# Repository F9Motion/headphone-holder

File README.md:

# Headphone Holder
A RGB cylender type headphone holder for airpods max type headphones.

# Why I did this
I ddin't know what to did today and take idea from forge keeper.
# Features
* Minimalistic design
* Wireless
* With RGB diodes
* Custom
# How it works
Raspberry pi pico do all work. It put to diodes signals and control them. MCP83731 is for battery and charge the battery.
# How to assemble
1. Print PCB from **JLCPCB**
2. Print **CAD** files
3. Order microcontrollers from **BOM** and solder it to PCB
4. Flash
# How to Flash
1. Install arduino IDE
2. Download firmware
3. Connect your PC to Raspberry pi pico
4. Upload firmware
# Bill Of Materials(BOM)
|Name             |Price|Link                     |
|-----------------|-----|-------------------------|
|Printing PCB     |$2   |JLCPCB no link           |
|Raspberry pi pico|$3.48|https://ali.click/eaneq1g|
|mcp73831         |$0.58|https://ali.click/mgneq13|
|Battery          |$7.26|https://ali.click/jpneq1o|
|bottom.step      |$0.6 |felament price           |
|top.step         |$1,19|felament price           |
# Credits
All work: Rasul

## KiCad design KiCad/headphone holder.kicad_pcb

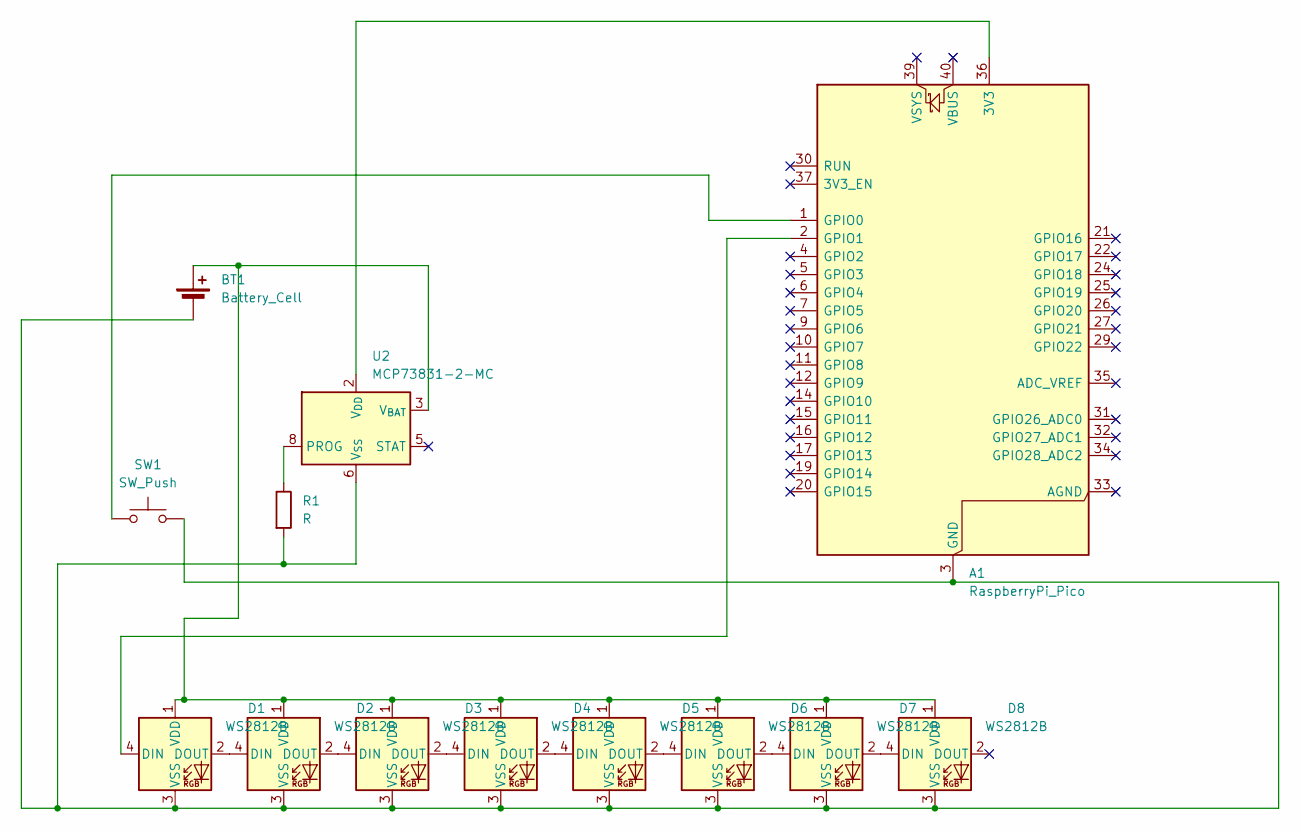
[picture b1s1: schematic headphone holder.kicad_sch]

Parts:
A1: RaspberryPi_Pico; RaspberryPi_Pico_Common_Unspecified
BT1: Battery_Cell; JST_PH_B2B-PH-K_1x02_P2.00mm_Vertical
D1, D2, D3, D4, D5, D6, D7, D8: WS2812B; LED_WS2812B_PLCC4_5.0x5.0mm_P3.2mm
R1: R; R_0201_0603Metric
SW1: SW_Push; SW_Cherry_MX_1.00u_PCB
U2: MCP73831-2-MC; DFN-8-1EP_3x2mm_P0.5mm_EP1.7x1.4mm

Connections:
unnamed: A1.36 (3V3), U2.1 (V_{DD}), U2.2 (V_{DD})
unnamed: A1.1 (GPIO0), SW1.1
unnamed: A1.2 (GPIO1), D1.4 (DIN)
unnamed: BT1.1 (+), D1.1 (VDD), D2.1 (VDD), D3.1 (VDD), D4.1 (VDD), D5.1 (VDD), D6.1 (VDD), D7.1 (VDD), D8.1 (VDD), U2.3 (V_{BAT}), U2.4 (V_{BAT})
unnamed: A1.3 (GND), A1.8 (GND), A1.13 (GND), A1.18 (GND), A1.23 (GND), A1.28 (GND), A1.38 (GND), BT1.2 (-), D1.3 (VSS), D2.3 (VSS), D3.3 (VSS), D4.3 (VSS), D5.3 (VSS), D6.3 (VSS), D7.3 (VSS), D8.3 (VSS), R1.2, SW1.2, U2.6 (V_{SS})
unnamed: D1.2 (DOUT), D2.4 (DIN)
unnamed: D2.2 (DOUT), D3.4 (DIN)
unnamed: D3.2 (DOUT), D4.4 (DIN)
unnamed: D4.2 (DOUT), D5.4 (DIN)
unnamed: D5.2 (DOUT), D6.4 (DIN)
unnamed: D6.2 (DOUT), D7.4 (DIN)
unnamed: D7.2 (DOUT), D8.4 (DIN)
unnamed: R1.1, U2.8 (PROG)

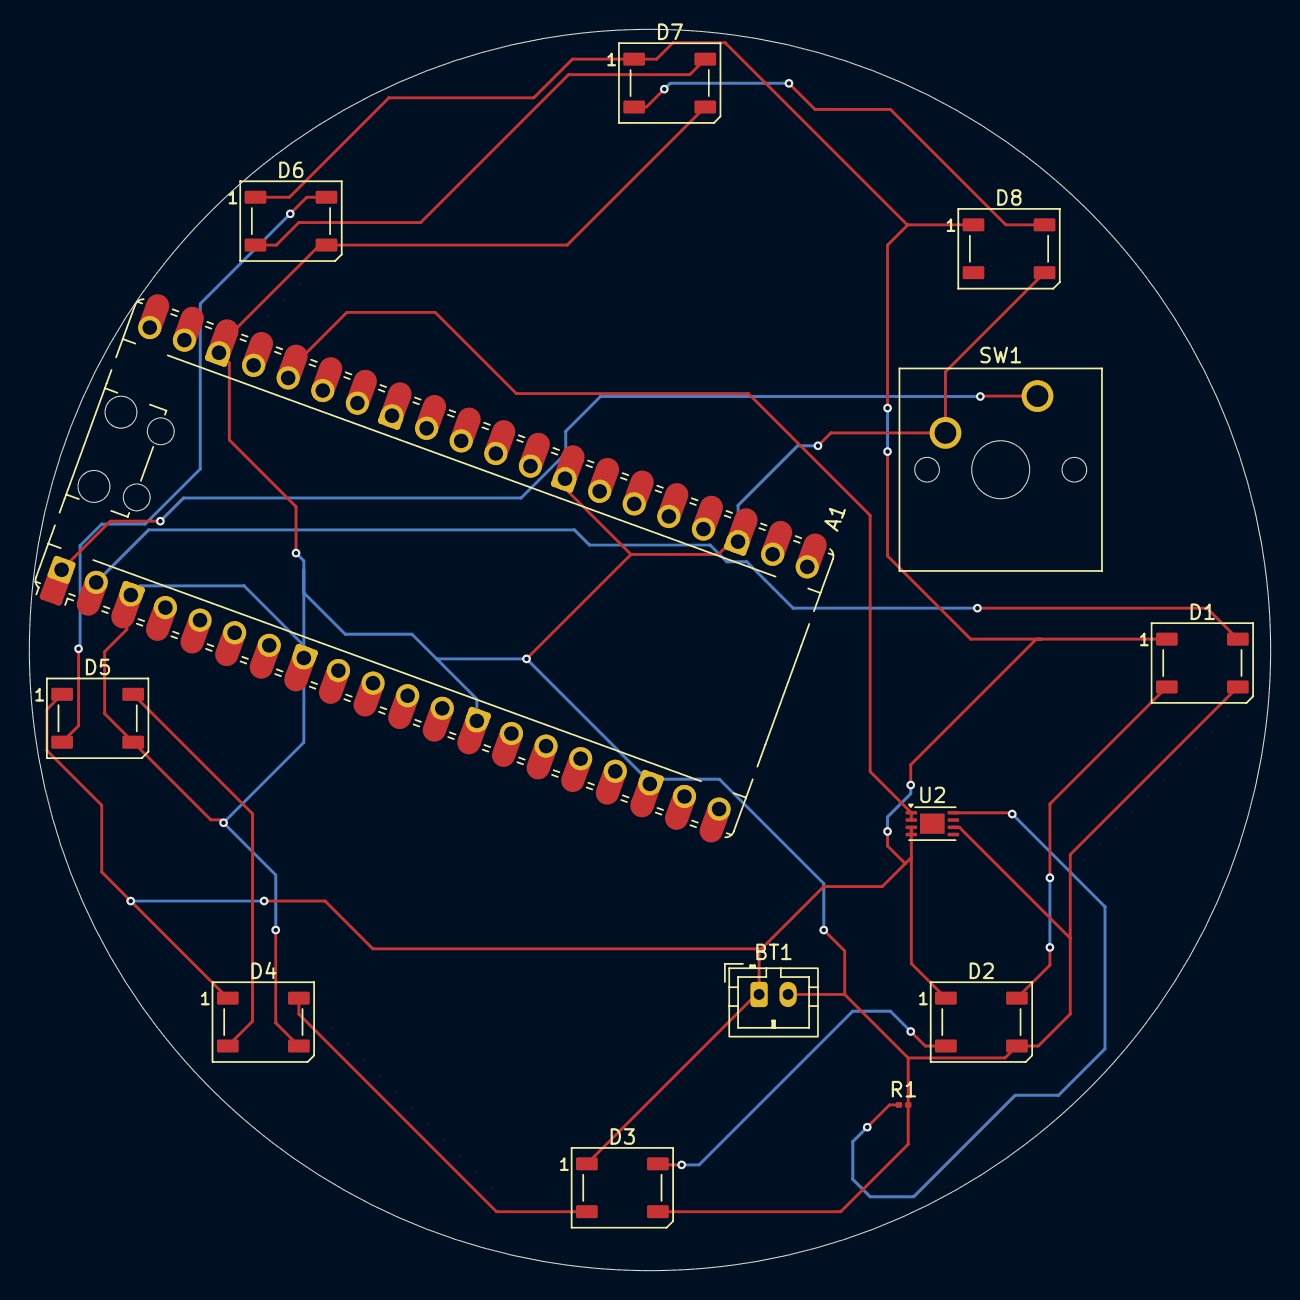
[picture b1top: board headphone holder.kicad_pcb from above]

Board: 2 copper layers, 85.6 x 85.6 mm, 13 parts (0 on the bottom side), 13 nets.
